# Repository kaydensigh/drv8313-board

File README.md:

# DRV8313 Board

An open-hardware **3-phase motor driver module** built around the Texas Instruments
[**DRV8313**](https://www.ti.com/lit/ds/symlink/drv8313.pdf) (three half-bridges, 8–60 V).
It drives BLDC/PMSM motors (3-PWM / FOC, e.g. with [SimpleFOC](https://simplefoc.com)),
and — because the three half-bridges and their enables are broken out independently —
also brushed-DC motors, solenoids, and 6-step/trapezoidal loads.

> Derived from the [SimpleFOCMini](https://github.com/simplefoc/SimpleFOCMini) board
> ([EasyEDA source](https://easyeda.com/the.skuric/simplefocmini)) and re-engineered for
> the DRV8313's full voltage range. It has since diverged substantially from the original
> (higher voltage, larger 4-layer board, on-board current limit, independent half-bridge
> enables), hence the separate project.

## Specifications

| | |
| --- | --- |
| Driver | DRV8313PWPR (HTSSOP-28, exposed thermal pad) |
| Supply voltage | **8–60 V** |
| Continuous current | **~1.5 A / phase** (1 oz copper, Tj ≤ 125 °C; ~2 A with airflow). The datasheet's 2.5 A/phase is a *peak* rating. |
| Logic level | 3.3 V (DRV8313 on-chip `V3P3OUT` regulator; no separate LDO). The `3.3V` header pin is an **output only — max 10 mA**; never drive it from the host. |
| Board | **50 × 50 mm**, 4-layer (Top / GND / GND / Bottom, 1 oz) |
| Control | 3× IN (PWM) + 3× independent EN (solder jumpers gang them for 3-PWM/FOC); nRESET / nSLEEP / nFAULT |
| Current limit | On-board comparator (50 mΩ shunt + jumper-set reference divider); raises `nCOMPO` flag on the header — host acts on it, no automatic shutdown |
| Connectors | 2×7 control header, 5-pos motor/VM terminal block, 2-pos power terminal block |

### Features beyond the original SimpleFOCMini

- **8–60 V** input (vs. 8–24 V) on a 4-layer board with inner ground planes.
- **On-board over-current detection** using the DRV8313's internal comparator (`COMPP`/`COMPN`):
  a 50 mΩ low-side shunt and a 3.3 V reference divider, with three solder jumpers (bridged by
  default) setting the trip point — all bridged ≈ 2.5 A, cut `SJ1` ≈ 1.05 A, cut `SJ2` ≈ 1.5 A,
  cut `SJ3` disables it. The comparator raises the open-drain `nCOMPO` flag on the header; it
  does not shut the bridge down by itself.
- **Independent half-bridge enables** (`EN1`/`EN2`/`EN3`, each brought out on the header) so the
  board can run brushed-DC / solenoid / 6-step loads. Two **solder jumpers on the board**
  (`EN1_EN2`, `EN2_EN3` — open by default) gang the three enables back together for the
  original 3-PWM/FOC drive: bridge both and a single host pin drives all three, with no wiring
  at the header.

## Renders

| Schematic | PCB (top) | PCB (bottom) |
| --- | --- | --- |
|  |  |  |

## Repository layout

| Path | Contents |
| --- | --- |
| [`KiCad/project/`](./KiCad/project/) | KiCad 10 source — schematic, PCB, project, and the `drv8313-board` project library (`.pretty` footprints + `.kicad_sym` symbols) |
| [`manufacturing/`](./manufacturing/) | Fabrication outputs: [`gerbers/`](./manufacturing/gerbers/) (Gerber + Excellon drill), [BOM](./manufacturing/drv8313-board-BOM.csv), [pick-and-place CPL](./manufacturing/drv8313-board-CPL.csv), and a [STEP](./manufacturing/drv8313-board.step) 3D model |
| [`docs/`](./docs/) | [`datasheets/`](./docs/datasheets/) — the DRV8313 datasheet (authoritative part reference) |
| [`tools/`](./tools/) | Headless helper scripts — JLCPCB part search, manufacturing-file regeneration, silk version bump ([`tools/README.md`](./tools/README.md)) |
| [`images/`](./images/) | Renders used above |

The design is maintained **only** in KiCad now; the original Altium / EasyEDA / PDF exports
have been removed. The manufacturing files are regenerated from the KiCad project with
[`tools/build_manufacturing.py`](./tools/build_manufacturing.py) (a `kicad-cli` wrapper).

## Bill of materials

The full BOM (with footprints) is [`manufacturing/drv8313-board-BOM.csv`](./manufacturing/drv8313-board-BOM.csv).
Each MPN below links to its LCSC product page; **Library** is the JLCPCB part class —
**Basic** and **Preferred** are fee-free, **Extended** parts each add a one-time setup fee.

| Designator | Value | Qty | MPN | Unit price | Library |
| --- | --- | --- | --- | --- | --- |
| C1 | 10nF 100V | 1 | [CL10B103KC8NNNC](https://www.lcsc.com/product-detail/multilayer-ceramic-capacitors-mlcc-smd-smt_samsung-electro-mechanics-cl10b103kc8nnnc_C84709.html) | $0.0058 | Extended |
| C2 | 100nF 16V | 1 | [CC0603KRX7R9BB104](https://www.lcsc.com/product-detail/multilayer-ceramic-capacitors-mlcc-smd-smt_yageo-cc0603krx7r9bb104_C14663.html) | $0.0194 | Basic |
| C3,C5 | 47uF 100V | 2 | [RVT2A470M1010](https://www.lcsc.com/product-detail/aluminum-electrolytic-capacitors-smd_honor-elec-rvt2a470m1010_C87862.html) | $0.1206 | Extended |
| C4 | 470nF | 1 | [CL10B474KA8NNNC](https://www.lcsc.com/product-detail/multilayer-ceramic-capacitors-mlcc-smd-smt_samsung-electro-mechanics-cl10b474ka8nnnc_C1623.html) | $0.0254 | Basic |
| C7,C8 | 100nF 100V | 2 | [CL10B104KC8NNNC](https://www.lcsc.com/product-detail/multilayer-ceramic-capacitors-mlcc-smd-smt_samsung-electro-mechanics-cl10b104kc8nnnc_C15725.html) | $0.0297 | Extended |
| H1 | PinHeader 2x7 2.54mm | 1 | [2.54-2\*7P Female](https://www.lcsc.com/product-detail/female-headers_boomele-boom-precision-elec-2-54-2-7p_C38844.html) | $0.1101 | Extended |
| LED1 | Yellow | 1 | [NCD0603Y2](https://www.lcsc.com/product-detail/led-indication-discrete_foshan-nationstar-optoelectronics-ncd0603y2_C89811.html) | $0.0194 | Preferred |
| P1 | TerminalBlock 5P 5.0mm | 1 | [DB126V-5.0-5P-GN-P](https://www.lcsc.com/product-detail/screw-terminal-blocks_dorabo-db126v-5-0-5p-gn-p_C2835160.html) | $0.2395 | Extended |
| R1-R3,R12 | 10kΩ | 4 | [0603WAF1002T5E](https://www.lcsc.com/product-detail/chip-resistor-surface-mount_uni-royal-uniroyal-elec-0603waf1002t5e_C25804.html) | $0.0078 | Basic |
| R5,R11 | 1kΩ | 2 | [0603WAF1001T5E](https://www.lcsc.com/product-detail/chip-resistor-surface-mount_uni-royal-uniroyal-elec-0603waf1001t5e_C21190.html) | $0.0024 | Basic |
| R8 | 50mΩ | 1 | [HoJLR2512-3W-50mR-1%](https://www.lcsc.com/product-detail/current-sense-resistors-shunt-resistors_milliohm-hojlr2512-3w-50mr-1_C2903475.html) | $0.0676 | Extended |
| R9 | 43kΩ | 1 | [0603WAF4302T5E](https://www.lcsc.com/product-detail/chip-resistor-surface-mount_uni-royal-uniroyal-elec-0603waf4302t5e_C23172.html) | $0.0076 | Preferred |
| R10 | 62kΩ | 1 | [0603WAF6202T5E](https://www.lcsc.com/product-detail/chip-resistor-surface-mount_uni-royal-uniroyal-elec-0603waf6202t5e_C23221.html) | $0.0092 | Preferred |
| TB_PWR1 | TerminalBlock 2P 5.0mm | 1 | [DB126V-5.0-2P-GN-P](https://www.lcsc.com/product-detail/screw-terminal-blocks_dorabo-db126v-5-0-2p-gn-p_C395849.html) | $0.0876 | Extended |
| U1 | DRV8313PWPR | 1 | [DRV8313PWPR](https://www.lcsc.com/product-detail/brushless-dc-bldc-motor-driver_texas-instruments-drv8313pwpr_C92482.html) | $1.4973 | Extended |

**Component cost ≈ $2.43/board in volume** (unit prices at JLCPCB's 100-piece tier, 2026-07-17;
U1 dominates). 8 parts are **Extended** (one-time setup fee each); the rest are fee-free.

**A small batch of 10 boards ≈ $55.53 in parts (~$5.55/board)**: $31.53 of components (JLCPCB
per-part assembly minimums + attrition applied) plus 8 × $3 Extended-part setup fees ($24). The
fixed fees amortise over larger runs. Excludes PCB fabrication, assembly labour and shipping.

Regenerate these from live prices with [`tools/gen_readme_bom.py`](./tools/gen_readme_bom.py)
(`--batch N` for a different run size); verify live stock with
[`tools/check_bom.py`](./tools/check_bom.py).

## Ordering

The board is designed to be fabricated and assembled at [JLCPCB](https://jlcpcb.com):

1. Upload `manufacturing/gerbers/` (zipped) for fabrication — 4-layer, 1 oz.
2. Use `manufacturing/drv8313-board-BOM.csv` and `manufacturing/drv8313-board-CPL.csv`
   for assembly. Every line carries an LCSC part number. Most parts are **fee-free** on
   JLCPCB — Basic or Preferred, no per-part setup fee — including the 43 k/62 k divider
   resistors (Preferred). The unavoidable **Extended** parts are the DRV8313 itself, the
   10 nF/100 V, 100 nF/100 V and 47 µF/100 V capacitors, the 50 mΩ current-sense shunt, and
   the three connectors. The connectors — `H1` (2×7 header), `P1` and `TB_PWR1` (5 mm screw terminal
   blocks) — are **through-hole**: order them via JLCPCB's through-hole assembly add-on or
   solder them by hand. Re-verify live stock before ordering — `tools/jlc_search.py` checks
   live stock/price (note: the 10 kΩ Basic resistor occasionally reads out of stock).

> **Status:** functional design — schematic and PCB are complete, fully routed, and both
> **DRC- and ERC-clean (0 violations)**. Not yet fabricated/validated in hardware. Review
> before ordering. Re-verify any time with
> [`tools/check_design.py`](./tools/check_design.py) (DRC + connectivity + ERC) and
> [`tools/check_bom.py`](./tools/check_bom.py) (live JLCPCB part stock).

## License

See [`LICENSE`](./LICENSE). This project inherits from the open-source SimpleFOCMini; please
also credit the original authors.

## Credits

Based on [**SimpleFOCMini**](https://github.com/simplefoc/SimpleFOCMini) by the
[SimpleFOC](https://simplefoc.com) project (Antun Skuric et al.).

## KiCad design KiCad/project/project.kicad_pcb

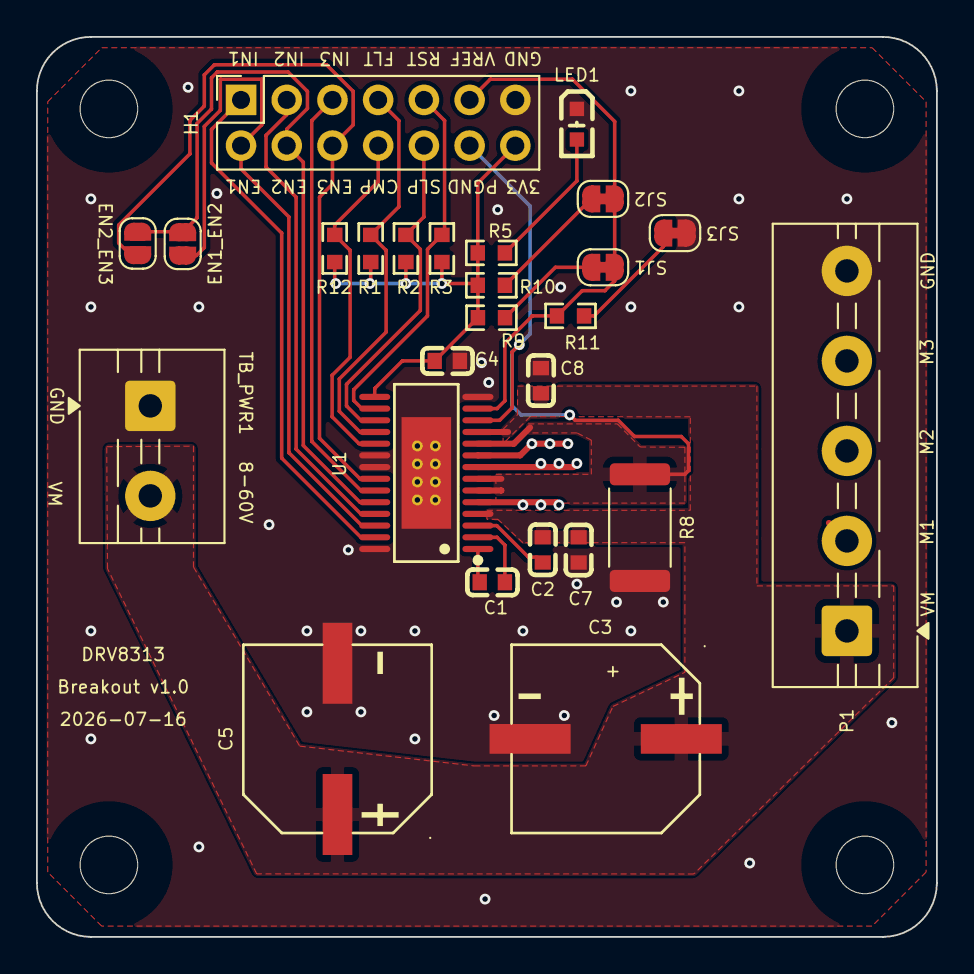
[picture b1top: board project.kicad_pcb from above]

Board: 4 copper layers, 50.0 x 50.0 mm, 30 parts (0 on the bottom side), 25 nets.

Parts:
C1: 10nF 100V; C0603
C2: 100nF 16V; C0603
C3, C5: 47uF 100V; CAP-SMD_BD10.0-L10.3-W10.3-FD-LS11.0
C4: 470nF; C0603
C7, C8: 100nF 100V; C0603
EN1_EN2, EN2_EN3: SolderJumper_2_Open; SolderJumper-2_P1.3mm_Open_RoundedPad1.0x1.5mm
H1: PinHeader 2x7 2.54mm; PinSocket_2x07_P2.54mm_Vertical
LED1: Yellow; LED0603-R-RD
MH1, MH2, MH3, MH4: MountingHole_3.2mm_M3
P1: TerminalBlock 5P 5.0mm; TerminalBlock_MaiXu_MX126-5.0-05P_1x05_P5.00mm
R1, R2, R3, R12: 10kΩ; R0603
R5, R11: 1kΩ; R0603
R8: 50mΩ; R_2512_6332Metric
R9: 43kΩ; R0603
R10: 62kΩ; R0603
SJ1, SJ2, SJ3: JMP; SolderJumper-2_P1.3mm_Bridged_RoundedPad1.0x1.5mm
TB_PWR1: TerminalBlock 2P 5.0mm; TerminalBlock_MaiXu_MX126-5.0-02P_1x02_P5.00mm
U1: DRV8313PWPR; HTSSOP-28_L9.8-W4.5-P0.65-LS6.6-BL-EP

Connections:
3.3V: C4.2, H1.14, R1.1, R2.1, R3.1, R5.1, R9.1, R10.1, R12.2, U1.15 (V3P3OUT)
EN1: EN1_EN2.1 (A), H1.2, U1.26 (EN1)
EN2: EN1_EN2.2 (B), EN2_EN3.1 (A), H1.4, U1.24 (EN2)
EN3: EN2_EN3.2 (B), H1.6, U1.22 (EN3)
GND: C3.2, C4.1, C5.2, C7.1, C8.1, H1.13, LED1.2 (C), P1.5, R8.2, SJ3.2 (B), TB_PWR1.1, U1.14 (GND), U1.20 (GND), U1.21 (NC), U1.28 (GND), U1.29 (EP)
IN1: H1.1, U1.27 (IN1)
IN2: H1.3, U1.25 (IN2)
IN3: H1.5, U1.23 (IN3)
M1: P1.2, U1.5 (OUT1)
M2: P1.3, U1.8 (OUT2)
M3: P1.4, U1.9 (OUT3)
unnamed: LED1.1 (A), R5.2
unnamed: R9.2, SJ1.1 (A)
unnamed: R10.2, SJ2.1 (A)
unnamed: R11.2, SJ3.1 (A)
unnamed: C1.2, U1.1 (CP1)
unnamed: C1.1, U1.2 (CP2)
unnamed: C2.2, U1.3 (VCP)
PGND: H1.12, R8.1, U1.6 (PGND1), U1.7 (PGND2), U1.10 (PGND3), U1.12 (COMPP)
VCC: C2.1, C3.1, C5.1, C7.2, C8.2, P1.1, TB_PWR1.2, U1.4 (VM), U1.11 (VM)
VREF: H1.11, R11.1, SJ1.2 (B), SJ2.2 (B), U1.13 (COMPN)
nCOMPO: H1.8, R12.1, U1.19 (COMPO#)
nFlt: H1.7, R1.2, U1.18 (FAULT#)
nRes: H1.9, R3.2, U1.16 (RESET#)
nSlp: H1.10, R2.2, U1.17 (SLEEP#)

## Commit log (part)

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2026-06-18 Redo schematic layout.
2026-06-26 Claude's attempt at redoing the whole layout.
2026-06-26 Manual layout.
